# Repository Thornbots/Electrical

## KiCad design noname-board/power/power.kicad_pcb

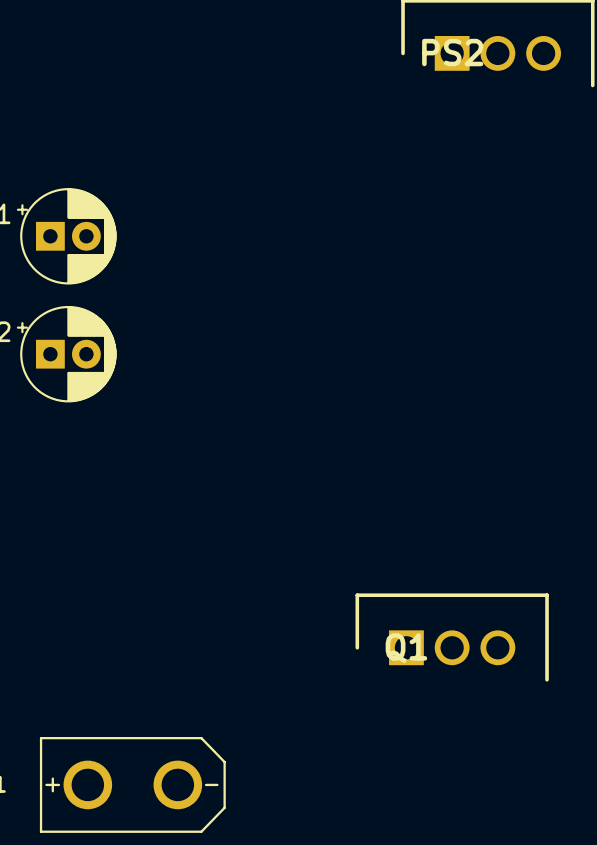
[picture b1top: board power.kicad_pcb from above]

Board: 2 copper layers, 5 parts (0 on the bottom side), 3 nets, no tracks yet.

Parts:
C1: .47uF; CP_Radial_D5.0mm_P2.00mm
C2: 22uF; CP_Radial_D5.0mm_P2.00mm
J1: Conn_01x02_Pin; XT30UPB-M
PS2: LM1084IT-3.3_NOPB; TO254P470X1028X1955-3P
Q1: LM2940CT-5.0_NOPB; TO254P470X1028X1955-3P

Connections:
5V: C2.1, Q1.3 (OUT)
24V: C1.1, Q1.1 (IN)
GND: C1.2, C2.2, PS2.2 (OUT), Q1.2 (GND)
